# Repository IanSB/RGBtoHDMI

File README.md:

# RGBtoHDMI

The RGBtoHDMI interface converts the "digital" RGB video signal from
the BBC Micro or Electron to HDMI compatible with most modern
TV/Monitors. The interface comprises a Raspberry Pi Zero and a
specially designed Hat containing a small CPLD. Custom firmware on the
Raspberry Pi, in conjunction with the CPLD, is able to correctly
sample each of the Beeb's video modes to give a pixel-perfect
rendition.

For more information, see the project [Wiki](../../wiki).  
Assembled boards available here:  
https://github.com/IanSB/RGBtoHDMI/wiki/Assembled-boards-for-sale

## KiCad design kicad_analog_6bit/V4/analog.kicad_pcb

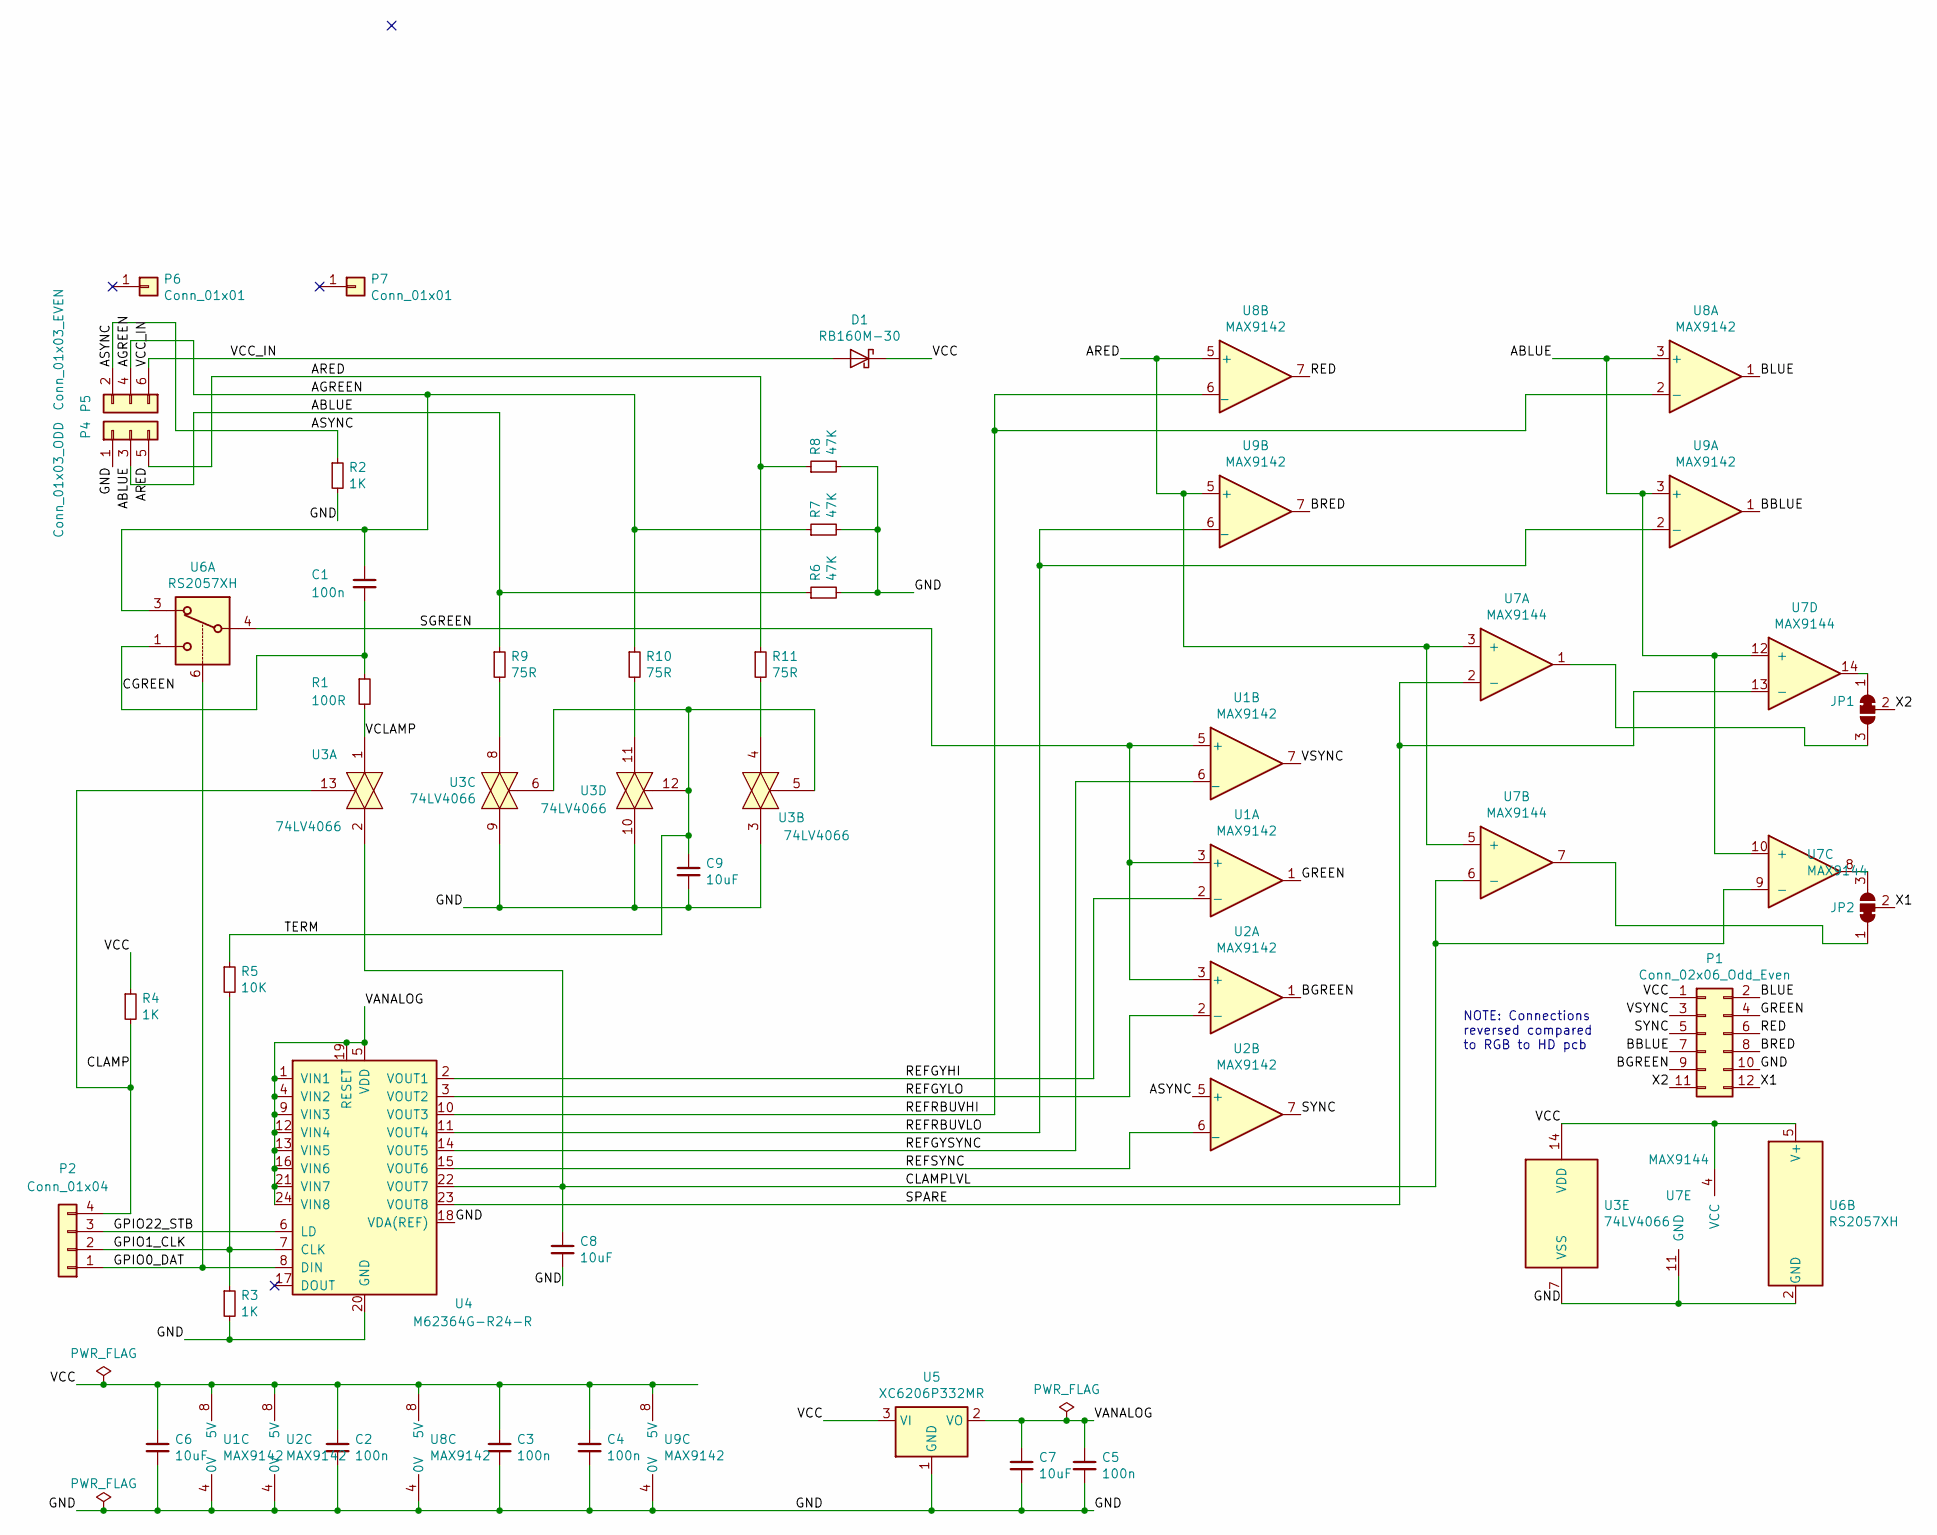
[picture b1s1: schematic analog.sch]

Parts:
C1, C2, C3, C4, C5: 100n; C_0805_2012Metric_Pad1.15x1.40mm_HandSolder
C6, C7, C8, C9: 10uF; C_0805_2012Metric_Pad1.15x1.40mm_HandSolder
D1: RB160M-30; D_SOD-123
JP1, JP2: SolderJumper_3_Bridged12; SolderJumper-3_P1.3mm_Bridged12_RoundedPad1.0x1.5mm
P1: Conn_02x06_Odd_Even; PinSocket_2x06_P2.54mm_Horizontal
P2: Conn_01x04; PinHeader_1x04_P2.54mm_Vertical
P4: Conn_01x03_ODD; Harwin_M20-89003xx_1x03_P2.54mm_Horizontal_Custom_ODD2
P5: Conn_01x03_EVEN; Harwin_M20-89003xx_1x03_P2.54mm_Horizontal_Custom_EVEN2
P6, P7: Conn_01x01; PinHeader_1x01_P2.54mm_Vertical
R1: 100R; R_0805_2012Metric_Pad1.15x1.40mm_HandSolder
R2, R3, R4: 1K; R_0805_2012Metric_Pad1.15x1.40mm_HandSolder
R5: 10K; R_0805_2012Metric_Pad1.15x1.40mm_HandSolder
R6, R7, R8: 47K; R_0805_2012Metric_Pad1.15x1.40mm_HandSolder
R9, R10, R11: 75R; R_0805_2012Metric_Pad1.15x1.40mm_HandSolder
U1, U2, U8, U9: MAX9142; SOIC-8_3.9x4.9mm_P1.27mm
U3: 74LV4066; TSSOP-14_4.4x5mm_P0.65mm
U4: M62364G-R24-R; SSOP-24_5.3x8.2mm_P0.65mm
U5: XC6206P332MR; SOT-23_Handsoldering
U6: RS2057XH; SOT-23-6_Handsoldering
U7: MAX9144; SOIC-14_3.9x8.7mm_P1.27mm

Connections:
/ABLUE: P4.3, R6.1, R9.1, U7.10 (+), U7.12 (+), U8.3 (+), U9.3 (+)
/AGREEN: C1.1, P5.4, R7.1, R10.1, U6.3
/ARED: P4.5, R8.1, R11.1, U7.3 (+), U7.5 (+), U8.5 (+), U9.5 (+)
/ASYNC: P5.2, R2.1, U2.5 (+)
/BBLUE: P1.7, U9.1
/BGREEN: P1.9, U2.1
/BLUE: P1.2, U8.1
/BRED: P1.8, U9.7
/CGREEN: C1.2, R1.1, U6.1
/CLAMP: P2.4, R4.2, U3.13
/CLAMPLVL: C8.1, U3.2, U4.22 (VOUT7), U7.6 (-), U7.9 (-)
/GND: C2.2, C3.2, C4.2, C5.2, C6.2, C7.2, C8.2, C9.2, P1.10, P4.1, R2.2, R3.2, R6.2, R7.2, R8.2, U1.4 (0V), U2.4 (0V), U3.3, U3.7 (VSS), U3.9, U3.10, U4.18 (VDA(REF)), U4.20 (GND), U5.1 (GND), U6.2 (GND), U7.11 (GND), U8.4 (0V), U9.4 (0V)
/GPIO0_DAT: P2.1, U4.8 (DIN), U6.6
/GPIO1_CLK: P2.2, R3.1, R5.2, U4.7 (CLK)
/GPIO22_STB: P2.3, U4.6 (LD)
/GREEN: P1.4, U1.1
/RED: P1.6, U8.7
/REFGYHI: U1.2 (-), U4.2 (VOUT1)
/REFGYLO: U2.2 (-), U4.3 (VOUT2)
/REFGYSYNC: U1.6 (_), U4.14 (VOUT5)
/REFRBUVHI: U4.10 (VOUT3), U8.2 (-), U8.6 (_)
/REFRBUVLO: U4.11 (VOUT4), U9.2 (-), U9.6 (_)
/REFSYNC: U2.6 (_), U4.15 (VOUT6)
/SGREEN: U1.3 (+), U1.5 (+), U2.3 (+), U6.4
/SPARE: U4.23 (VOUT8), U7.2 (-), U7.13 (-)
/SYNC: P1.5, U2.7
/TERM: C9.1, R5.1, U3.5, U3.6, U3.12
/VANALOG: C5.1, C7.1, U4.1 (VIN1), U4.4 (VIN2), U4.5 (VDD), U4.9 (VIN3), U4.12 (VIN4), U4.13 (VIN5), U4.16 (VIN6), U4.19 (RESET), U4.21 (VIN7), U4.24 (VIN8), U5.2 (VO)
/VCC: C2.1, C3.1, C4.1, C6.1, D1.1 (K), P1.1, R4.1, U1.8 (5V), U2.8 (5V), U3.14 (VDD), U5.3 (VI), U6.5 (V+), U7.4 (VCC), U8.8 (5V), U9.8 (5V)
/VCC_IN: D1.2 (A), P5.6
/VCLAMP: R1.2, U3.1
/VSYNC: P1.3, U1.7
/X1: JP2.2 (C), P1.12
/X2: JP1.2 (C), P1.11
unnamed: JP1.1 (A), U7.14
unnamed: JP1.3 (B), U7.1
unnamed: JP2.1 (A), U7.7
unnamed: JP2.3 (B), U7.8
unnamed: R9.2, U3.8
unnamed: R10.2, U3.11
unnamed: R11.2, U3.4

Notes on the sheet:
NOTE: Connections reversed compared to RGB to HD pcb

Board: 2 copper layers, 38 parts (6 on the bottom side), 41 nets, no tracks yet.

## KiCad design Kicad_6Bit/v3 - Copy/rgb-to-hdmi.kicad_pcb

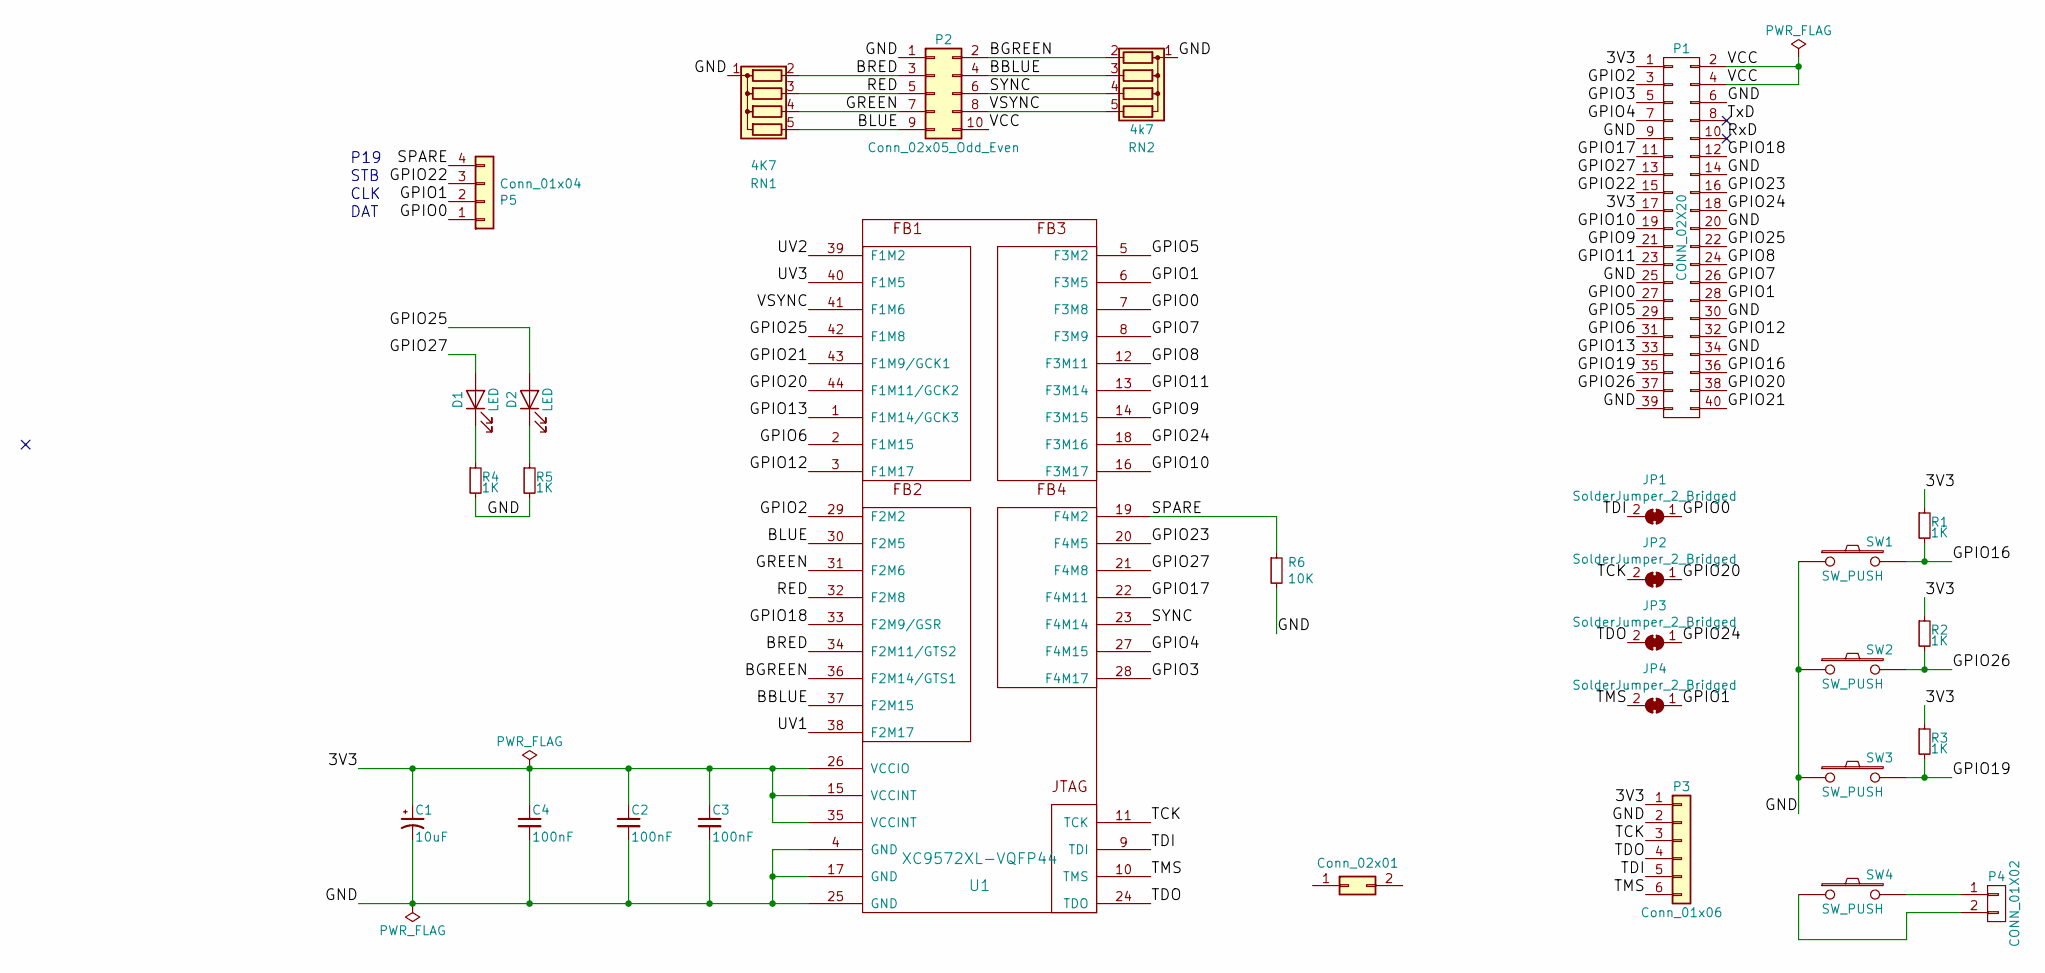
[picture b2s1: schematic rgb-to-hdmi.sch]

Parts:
C1: 10uF; C_0805_2012Metric_Pad1.15x1.40mm_HandSolder
C2, C3, C4: 100nF; C_0805_2012Metric_Pad1.15x1.40mm_HandSolder
D1, D2: LED; LED_D1.8mm_W3.3mm_H2.4mm
J2: Conn_02x01; PinHeader_2x01_P2.54mm_Horizontal
JP1, JP2, JP3, JP4: SolderJumper_2_Bridged; SolderJumper-2_P1.3mm_Bridged_RoundedPad1.0x1.5mm
P1: CONN_02X20; PinSocket_2x20_P2.54mm_Vertical
P2: Conn_02x05_Odd_Even; PinHeader_2x05_P2.54mm_Horizontal
P3: Conn_01x06; PinHeader_1x06_P2.54mm_Vertical
P4: CONN_01X02; PinSocket_1x02_P2.54mm_Vertical
P5: Conn_01x04; PinSocket_1x04_P2.54mm_Vertical
R1, R2, R3, R4, R5: 1K; R_0805_2012Metric_Pad1.15x1.40mm_HandSolder
R6: 10K; R_0805_2012Metric_Pad1.15x1.40mm_HandSolder
RN1: 4K7; R_Array_SIP5
RN2: 4k7; R_Array_SIP5
SW1, SW2, SW3, SW4: SW_PUSH; SW_PUSH_6mm_H5mm
U1: XC9572XL-VQFP44; LQFP-44_10x10mm_P0.8mm

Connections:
/3V3: C1.1, C2.1, C3.1, C4.1, P1.1, P1.17, P3.1, R1.1, R2.1, R3.1, U1.15 (VCCINT), U1.26 (VCCIO), U1.35 (VCCINT)
/BBLUE: P2.4, RN2.3 (R2), U1.37 (F2M15)
/BGREEN: P2.2, RN2.2 (R1), U1.36 (F2M14/GTS1)
/BLUE: P2.9, RN1.5 (R4), U1.30 (F2M5)
/BRED: P2.3, RN1.2 (R1), U1.34 (F2M11/GTS2)
/GND: C1.2, C2.2, C3.2, C4.2, P1.6, P1.9, P1.14, P1.20, P1.25, P1.30, P1.34, P1.39, P2.1, P3.2, R4.2, R5.2, R6.2, RN1.1 (common), RN2.1 (common), SW1.1, SW2.1, SW3.1, U1.4 (GND), U1.17 (GND), U1.25 (GND)
/GPIO0: JP1.1 (A), P1.27, P5.1, U1.7 (F3M8)
/GPIO1: JP4.1 (A), P1.28, P5.2, U1.6 (F3M5)
/GPIO2: P1.3, U1.29 (F2M2)
/GPIO3: P1.5, U1.28 (F4M17)
/GPIO4: P1.7, U1.27 (F4M15)
/GPIO5: P1.29, U1.5 (F3M2)
/GPIO6: P1.31, U1.2 (F1M15)
/GPIO7: P1.26, U1.8 (F3M9)
/GPIO8: P1.24, U1.12 (F3M11)
/GPIO9: P1.21, U1.14 (F3M15)
/GPIO10: P1.19, U1.16 (F3M17)
/GPIO11: P1.23, U1.13 (F3M14)
/GPIO12: P1.32, U1.3 (F1M17)
/GPIO13: P1.33, U1.1 (F1M14/GCK3)
/GPIO16: P1.36, R1.2, SW1.2
/GPIO17: P1.11, U1.22 (F4M11)
/GPIO18: P1.12, U1.33 (F2M9/GSR)
/GPIO19: P1.35, R3.2, SW3.2
/GPIO20: JP2.1 (A), P1.38, U1.44 (F1M11/GCK2)
/GPIO21: P1.40, U1.43 (F1M9/GCK1)
/GPIO22: P1.15, P5.3; also elsewhere on the board
/GPIO23: P1.16, U1.20 (F4M5)
/GPIO24: JP3.1 (A), P1.18, U1.18 (F3M16)
/GPIO25: D2.2 (A), P1.22, U1.42 (F1M8)
/GPIO26: P1.37, R2.2, SW2.2
/GPIO27: D1.2 (A), P1.13, U1.21 (F4M8)
/GREEN: P2.7, RN1.4 (R3), U1.31 (F2M6)
/RED: P2.5, RN1.3 (R2), U1.32 (F2M8)
/RxD: P1.10
/SPARE: P5.4, R6.1, U1.19 (F4M2); also elsewhere on the board
/SYNC: P2.6, RN2.4 (R3), U1.23 (F4M14)
/TCK: JP2.2 (B), P3.3, U1.11 (TCK)
/TDI: JP1.2 (B), P3.5, U1.9 (TDI)
/TDO: JP3.2 (B), P3.4, U1.24 (TDO)
/TMS: JP4.2 (B), P3.6, U1.10 (TMS)
/TxD: P1.8
/UV1: U1.38 (F2M17)
/UV2: U1.39 (F1M2)
/UV3: U1.40 (F1M5)
/VCC: P1.2, P1.4, P2.10
/VSYNC: P2.8, RN2.5 (R4), U1.41 (F1M6)
unnamed: D1.1 (K), R4.1
unnamed: D2.1 (K), R5.1
unnamed: P4.1, SW4.2
unnamed: P4.2, SW4.1

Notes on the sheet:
DAT
CLK
STB
P19

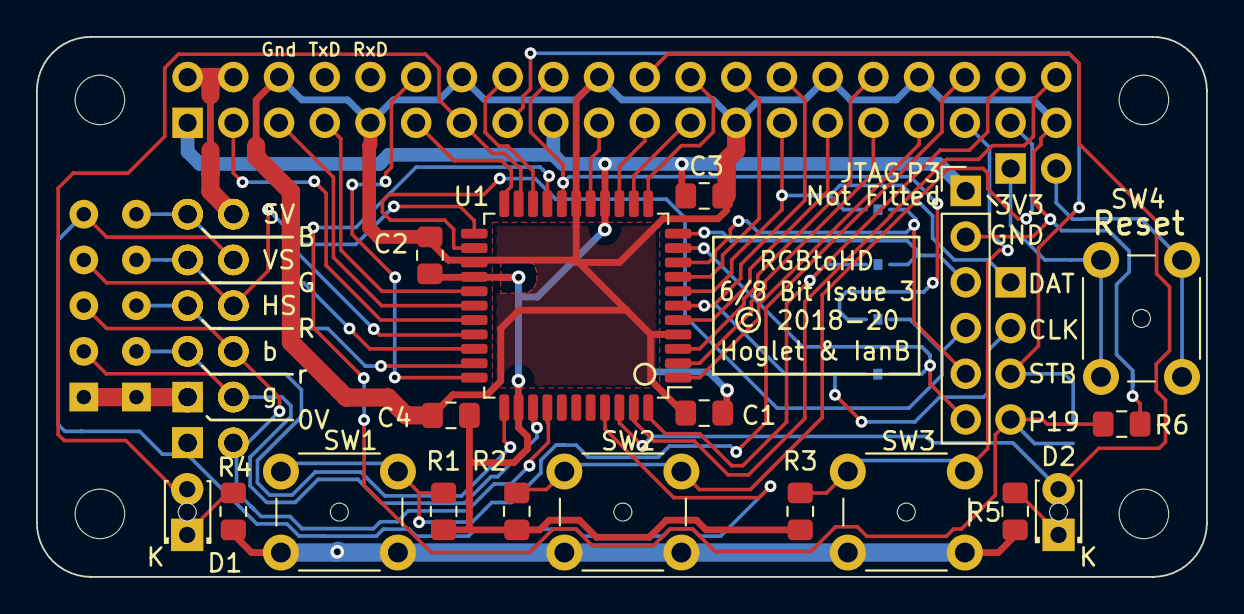
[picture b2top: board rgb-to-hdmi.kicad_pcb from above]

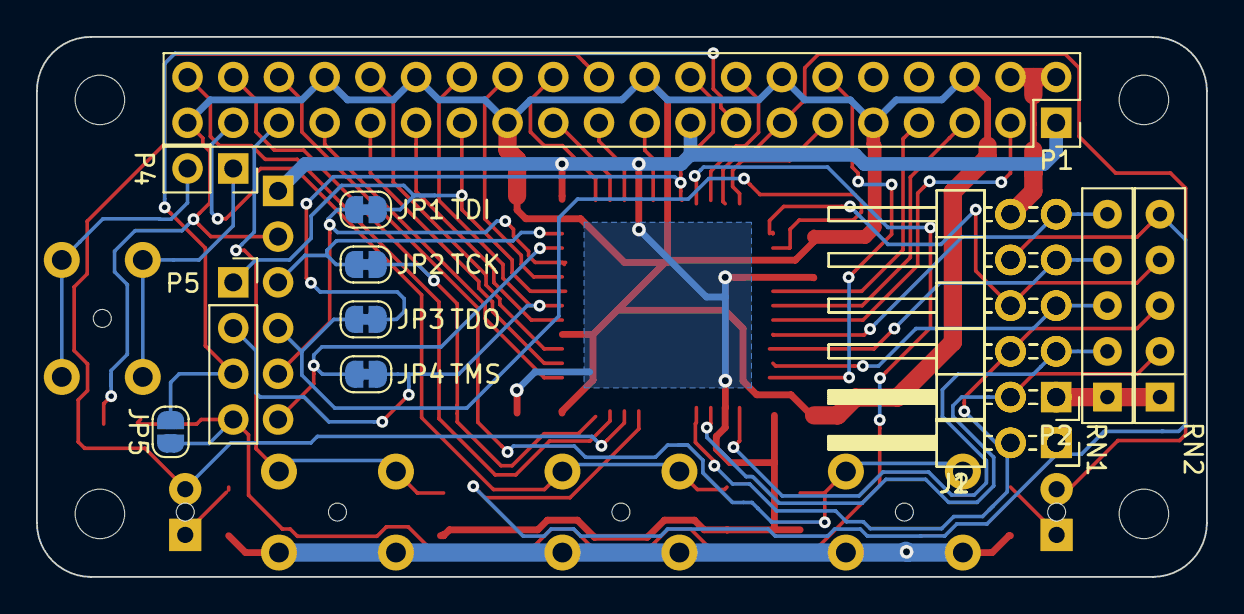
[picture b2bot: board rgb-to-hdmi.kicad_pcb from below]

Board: 2 copper layers, 65.0 x 30.0 mm, 37 parts (13 on the bottom side), 46 nets.

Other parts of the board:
 : mountinghole_1mm
 #2,  #3,  #4,  #5,  #6: mountinghole_1mm
J1: Conn_02x06_Odd_Even; PinHeader_2x06_P2.54mm_Horizontal
JP5: SolderJumper_2_Open; SolderJumper-2_P1.3mm_Open_RoundedPad1.0x1.5mm

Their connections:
/GPIO22: JP5.2; also elsewhere on the board
/SPARE: JP5.1; also elsewhere on the board

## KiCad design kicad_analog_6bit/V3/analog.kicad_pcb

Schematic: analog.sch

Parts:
C1, C2, C3, C4, C5: 100n; C_0805_2012Metric_Pad1.15x1.40mm_HandSolder
C6, C7, C8, C9: 10uF; C_0805_2012Metric_Pad1.15x1.40mm_HandSolder
D1: D_Schottky; D_0805_2012Metric_Pad1.15x1.40mm_HandSolder
JP1, JP2: SolderJumper_3_Bridged12; SolderJumper-3_P1.3mm_Bridged12_RoundedPad1.0x1.5mm
P1: Conn_02x06_Odd_Even; PinSocket_2x06_P2.54mm_Horizontal
P2: Conn_01x04; PinHeader_1x04_P2.54mm_Vertical
P3: Conn_01x06; Molex_PicoBlade_53048-0610_1x06_P1.25mm_Horizontal
P6, P7: Conn_01x01; PinHeader_1x01_P2.54mm_Vertical
R1: 75R; R_0805_2012Metric_Pad1.15x1.40mm_HandSolder
R2, R3, R4: 1K; R_0805_2012Metric_Pad1.15x1.40mm_HandSolder
R5, R6, R7, R8: 10K; R_0805_2012Metric_Pad1.15x1.40mm_HandSolder
R9, R10, R11: 68R; R_0805_2012Metric_Pad1.15x1.40mm_HandSolder
U1, U2: MAX9108; SOIC-14_3.9x8.7mm_P1.27mm
U3: MAX4610; SOIC-14_3.9x8.7mm_P1.27mm
U4: MAX5259EEE+; QSOP-16_3.9x4.9mm_P0.635mm
U5: MCP1754S-3302xCB; SOT-23_Handsoldering
U6: TS5A3159ADBVR; SOT-23-6_Handsoldering
U7: MAX9108-Comparator; SOIC-14_3.9x8.7mm_P1.27mm

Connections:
/ABLUE: P3.3, R6.1, R9.1, U2.3 (+), U2.5 (+), U7.10 (+), U7.12 (+)
/AGREEN: C1.1, P3.4, R7.1, R10.1, U6.3
/ARED: P3.5, R8.1, R11.1, U2.10 (+), U2.12 (+), U7.3 (+), U7.5 (+)
/ASYNC: P3.2, R2.1, U1.10 (+)
/BBLUE: P1.7, U2.7
/BGREEN: P1.9, U1.7
/BLUE: P1.2, U2.1
/BRED: P1.8, U2.8
/CGREEN: C1.2, R1.1, U6.1
/CLAMP: P2.4, R4.2, U3.13
/CLAMPLVL: C8.1, U3.2, U4.9 (OUTG), U7.6 (-), U7.9 (-)
/GND: C2.2, C3.2, C4.2, C5.2, C6.2, C7.2, C8.2, C9.2, P1.10, P3.1, R2.2, R3.2, R6.2, R7.2, R8.2, U1.11 (GND), U2.11 (GND), U3.3, U3.7 (VSS), U3.9, U3.10, U4.3 (GND), U4.6 (LDAC), U5.1 (GND), U6.2, U7.11 (GND)
/GPIO0_DAT: P2.1, U4.13 (DIN), U6.6
/GPIO1_CLK: P2.2, R3.1, R5.2, U4.12 (SCLK)
/GPIO22_STB: P2.3, U4.11 (CS)
/GREEN: P1.4, U1.1
/RED: P1.6, U2.14
/REFGYHI: U1.2 (-), U4.2 (OUTA)
/REFGYLO: U1.6 (-), U4.1 (OUTB)
/REFGYSYNC: U1.13 (-), U4.7 (OUTE)
/REFRBUVHI: U2.2 (-), U2.13 (-), U4.16 (OUTC)
/REFRBUVLO: U2.6 (-), U2.9 (-), U4.15 (OUTD)
/REFSYNC: U1.9 (-), U4.8 (OUTF)
/SGREEN: U1.3 (+), U1.5 (+), U1.12 (+), U6.4
/SPARE: U4.10 (OUTH), U7.2 (-), U7.13 (-)
/SYNC: P1.5, U1.8
/TERM: C9.1, R5.1, U3.5, U3.6, U3.12
/UV1: JP1.2, P1.11
/UV2: JP2.2, P1.12
/VANALOG: C5.1, C7.1, U4.4 (VDD), U4.5 (REF), U5.2 (VO)
/VCC: C2.1, C3.1, C4.1, C6.1, D1.1 (K), P1.1, R4.1, U1.4 (VCC), U2.4 (VCC), U3.14 (VDD), U5.3 (VI), U6.5, U7.4 (VCC)
/VCC_IN: D1.2 (A), P3.6
/VCLAMP: R1.2, U3.1
/VSYNC: P1.3, U1.14
unnamed: JP1.1, U7.14
unnamed: JP1.3, U7.1
unnamed: JP2.1, U7.7
unnamed: JP2.3, U7.8
unnamed: R9.2, U3.8
unnamed: R10.2, U3.11
unnamed: R11.2, U3.4

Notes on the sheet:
NOTE: Connections reversed compared to RGB to HD pcb

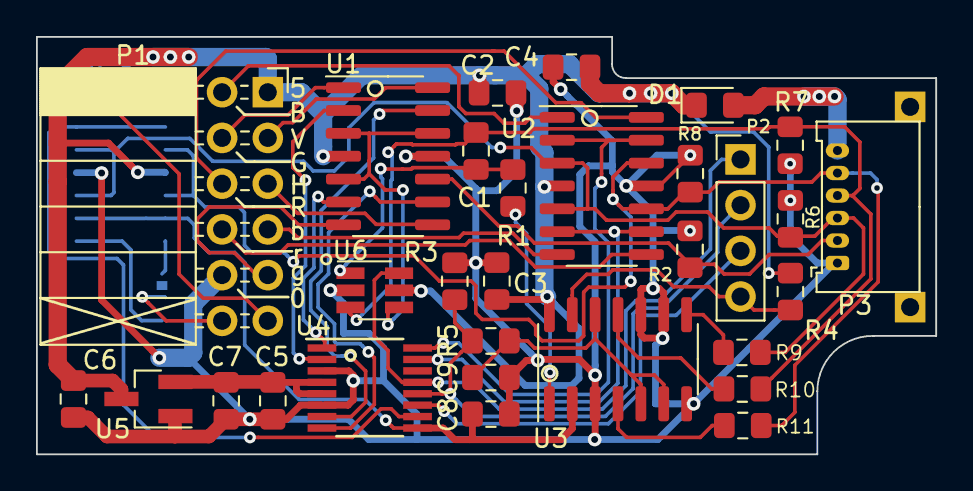
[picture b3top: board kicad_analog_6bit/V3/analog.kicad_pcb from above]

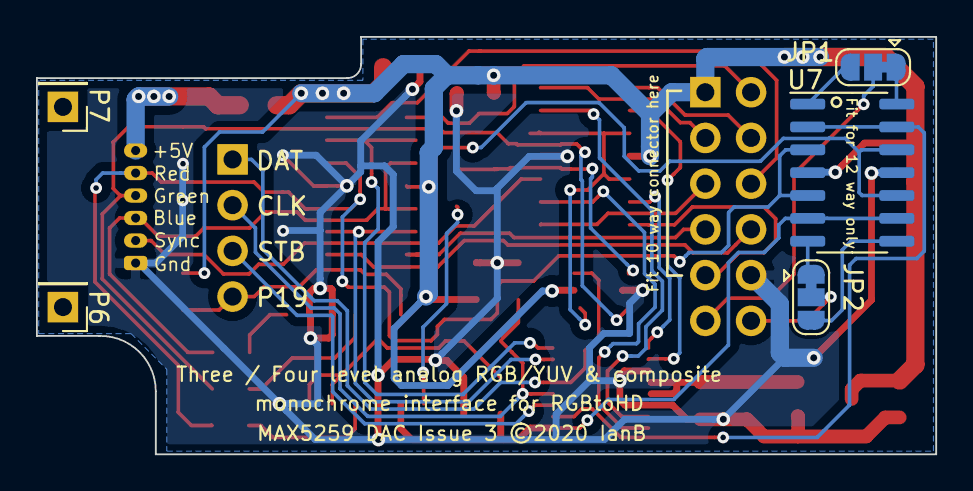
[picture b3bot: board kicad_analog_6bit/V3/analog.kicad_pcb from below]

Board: 2 copper layers, 50.0 x 23.2 mm, 35 parts (5 on the bottom side), 41 nets.

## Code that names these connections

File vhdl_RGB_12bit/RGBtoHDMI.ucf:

# Global Clock Nets
NET "clk" BUFG=CLK;

# 96MHz clock domain
NET "clk" TNM_NET = clk_period_grp_1;
TIMESPEC TS_clk_period_1 = PERIOD "clk_period_grp_1" 5.2ns HIGH;


NET "clk"       LOC = "P43";       # input  gpio21 (gclk)

NET "R3_I"      LOC = "P32";       # input
NET "G3_I"      LOC = "P31";       # input
NET "B3_I"      LOC = "P30";       # input
NET "R2_I"      LOC = "P34";       # input
NET "G2_I"      LOC = "P36";       # input
NET "B2_I"      LOC = "P37";       # input
NET "R1_I"      LOC = "P39";       # input  (was gpio26)
NET "G1_I"      LOC = "P40";       # input  (was gpio19)
NET "B1_I"      LOC = "P38";       # input  (was gpio16)
NET "R0_I"      LOC = "P21";       # input  (was gpio27)
NET "G0_I"      LOC = "P42";       # input  (was gpio25)
NET "B0_I"      LOC = "P18";       # input  (was gpio24)

NET "csync_I"   LOC = "P23";       # input
NET "vsync_I"   LOC = "P41";       # input  (connects to vsync)

NET "analog"    LOC = "P19";       # input  gpio22

NET "version"   LOC = "P33";       # input  gpio18 (gsr)

NET "sp_clken"  LOC = "P6";        # input  gpio1  (input only)

NET "quad(0)"   LOC = "P29";       # output gpio2
NET "quad(1)"   LOC = "P28";       # output gpio3
NET "quad(2)"   LOC = "P27";       # output gpio4
NET "quad(3)"   LOC = "P5";        # output gpio5
NET "quad(4)"   LOC = "P2";        # output gpio6
NET "quad(5)"   LOC = "P8";        # output gpio7
NET "quad(6)"   LOC = "P12";       # output gpio8
NET "quad(7)"   LOC = "P14";       # output gpio9
NET "quad(8)"   LOC = "P16";       # output gpio10
NET "quad(9)"   LOC = "P13";       # output gpio11
NET "quad(10)"  LOC = "P3";        # output gpio12
NET "quad(11)"  LOC = "P1";        # output gpio13

NET "psync"     LOC = "P22";       # output gpio17
NET "csync"     LOC = "P20";       # output gpio23

NET "quad(0)"   SLOW;
NET "quad(1)"   SLOW;
NET "quad(2)"   SLOW;
NET "quad(3)"   SLOW;
NET "quad(4)"   SLOW;
NET "quad(5)"   SLOW;
NET "quad(6)"   SLOW;
NET "quad(7)"   SLOW;
NET "quad(8)"   SLOW;
NET "quad(9)"   SLOW;
NET "quad(10)"  SLOW;
NET "quad(11)"  SLOW;
NET "psync"     SLOW;
NET "csync"     SLOW;

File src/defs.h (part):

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#define MAX_PIXEL_CLOCK     340.0 // 340MHz
#endif

// Enable multiple buffering and vsync based page flipping
#define MULTI_BUFFER

// The maximum number of buffers used by multi-buffering
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#define BIT_INTERLACED_VIDEO            0x80   // bit  7, if set then interlaced video detected or teletext enabled
#define BIT_CLEAR                      0x100   // bit  8, indicates the frame buffer should be cleared
#define BITDUP_ENABLE_FFOSD             0x100   // bit  8, indicates FFOSD is enabled
#define BIT_VSYNC                      0x200   // bit  9, indicates the red v sync indicator should be displayed
#define BIT_VSYNC_MARKER               0x400   // bit 10, indicates current line should be replaced by the red vsync indicator
#define BIT_DEBUG                      0x800   // bit 11, indicates the debug grid should be displayed

#define OFFSET_LAST_BUFFER 12        // bit 12-13 LAST_BUFFER
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#define GPLEV0_OFFSET     0x000034

#if defined(RPI4)
#define INTPEND2_OFFSET   0x00B204    //SMI interrupt (GPU # 48 used for vsync) is actually in IRQ0_PENDING1 on pi 4 (0xfe00b204)
#define PV2_INTSTAT       0x20a028
#else
#define INTPEND2_OFFSET   0x00B208
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#define GPIO_PULLDOWN   0x01
#define GPIO_PULLUP     0x02

#define SYNC_BIT_HSYNC_INVERTED   0x01      // bit  0, indicates hsync/composite sync is inverted
#define SYNC_BIT_VSYNC_INVERTED   0x02      // bit  1, indicates vsync is inverted
#define SYNC_BIT_COMPOSITE_SYNC   0x04      // bit  2, indicates composite sync
#define SYNC_BIT_MIXED_SYNC       0x08      // bit  3, indicates H and V syncs eored in CPLD
#define SYNC_BIT_INTERLACED       0x10      // bit  4, indicates interlaced sync detected
#define SYNC_BIT_MASK             0x07      // masks out bits 3 + 4

#define VSYNC_RETRY_MAX 10
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#define NTSC_Y_INVERT           0x20
#define NTSC_LAST_ARTIFACT      0x40
#define NTSC_LAST_ARTIFACT_SHIFT   6
#define NTSC_HDMI_BLANK_ENABLE  0x80        //not actually ntsc but uses a spare bit
#define NTSC_LAST_IIGS         0x100        //not actually ntsc but uses a spare bit
#define NTSC_LAST_IIGS_SHIFT       8
#define NTSC_FFOSD_ENABLE      0x200        //not actually ntsc but uses a spare bit
#define NTSC_DONE_FIRST        0x400
#define NTSC_RGB_INVERT        0x800

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#define YUV_VERSION 0x91

//these defines are adjusted for different clock speeds
#define FIELD_TYPE_THRESHOLD_BBC 39000            //  post frame sync times are ~22uS & ~54uS on beeb and ~34uS and ~66uS on Amiga so threshold of 45uS covers both
#define FIELD_TYPE_THRESHOLD_AMIGA 45000          //  post frame sync times are ~22uS & ~54uS on beeb and ~34uS and ~66uS on Amiga so threshold of 45uS covers both
#define ELK_LO_FIELD_SYNC_THRESHOLD 150000  // 150uS
#define ELK_HI_FIELD_SYNC_THRESHOLD 170000  // 170uS
#define ODD_THRESHOLD 22500
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#define BBC_HSYNC_THRESHOLD 6144
#define NORMAL_HSYNC_THRESHOLD 9000
#define BLANKING_HSYNC_THRESHOLD 14000
#define EQUALISING_THRESHOLD 3400      // equalising pulses are half sync pulse length and must be filtered out
#define FRAME_MINIMUM 10000000         // 10ms
#define FRAME_TIMEOUT 30000000         // 30ms which is over a frame / field @ 50Hz (20ms)
#define LINE_MINIMUM 10000             // 10uS
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
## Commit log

2020-02-16 Experimental V3 analog layout using GPIOs 0 & 1 to control termination
2020-02-16 Separate termination of Y & UV controlled from GPIO 0 & 1
2020-02-16 Support inverted termination including CPLD programming
2020-02-16 Update issue 3 with normally closed DG441
2020-02-17 Analog V3 non-inverted 14 pin
2020-02-17 Update profiles
2020-02-18 V3 PCB layout with MAX4610
2020-02-18 Change CPLD programming to have an average voltage below the logic 0 threshold
2020-02-18 Update code for latest analog hardware mods
2020-02-19 Update pcb with AC/DC switch
2020-02-19 Update for AC/DC input option
2020-02-21 V3 pcb plus some older alternatives
2020-02-21 Tweaks to V3 analog PCB
2020-02-22 Updated analog board
2020-02-22 Updated 8 bit
2020-02-22 Updated 8 bit hat
2020-02-22 Update profiles for ac/dc coupling
2020-02-22 Update ac/dc switch and analog driver
2020-06-17 Initial Circuit for issue 4
2021-07-05 Add support for CPLD v94 with 9 bpp + blank and 1bpp on vsync
2021-07-05 Further support for 1bpp vsync and auto config sample phasing
2021-07-06 Ignore flashing cursors when auto calibrating
2021-07-06 Optimise line capture loop and fix edge bug in NTSC artifact mode
2021-07-06 Improve sync loss handling
2021-07-06 Fix equivalence calculation
2021-10-29 Mark screen as cacheable
2021-10-29 Add L1 data cache clean
2022-01-01 Correct return value
    Return value of 0 = error
2024-01-25 Use parallel register transfer
2024-03-12 Add Nascom 1 & update Nascom 2 profiles
2024-03-12 Update test profiles
2024-03-12 Add Zenith Z110 profile
2024-03-17 Update default profile
2024-03-17 Update C64 profiles
2024-03-17 Update Sam Coupe profile
2024-03-17 Update 2560x1440 resolution
2024-03-17 Add 2560x1600 and 2048x1536 resolutions
2024-03-17 Add integer scaling preference setting and fix some scaling issues
2024-03-19 Fix some more integer scaling issues and add 9 bit lumacode
2024-03-20 Add support for 2560x1600 resolution
2024-03-20 Force DVI mode when auto detecting for blacklisted monitors
2024-03-24 Invert logic of _ profile hiding with mono/lumacode boards
2024-03-24 Update profiles for inverted _ hiding logic
2024-03-24 Add TI-990 VDT911 50Hz profile
2024-03-25 Further updates for inverted _ logic
2024-04-06 Update monitor blacklist
2024-04-23 Add BBC CPLD Limited Test profile
2024-04-23 Update BBC Nula profiles
2024-04-23 Update firmware
2024-04-23 Update default.txt in Amiga configs
2024-04-23 Update default.txt handling for single button mode and cpld firmware dir
2024-05-01 Update Mac profiles
2024-05-08 Reverse order of mode7 calibration
2024-05-08 Initial HDMI audio support including WAV player
2024-05-12 Clear screen when loading wav
2024-05-12 Update wav logging
2024-05-13 Move GPU capture code from VPU1 to VPU0
2024-06-14 Update NuLA profiles
2024-06-15 Update profiles for v9.5 RGB firmware
2024-06-16 Add mono palette option for analog V/Hsync, fix firmware update message & fix hang with GPU capture
2024-06-16 Update CPLD firmware release folder
2024-06-16 Add border setting to create profile menu
2024-06-16 Remove dedicated sync register in GPU comms
2024-06-17 Add analog profiles for video(B)+Hsync(S)+Vsync(G) sources
2024-06-30 Add zx81 vLA81 profile
2024-06-30 Change GPU comms to use 7 data registers
2024-09-08 Revert order of mode 7 calibration
2024-10-15 Update BBC digital test profiles
2024-10-15 Update BBC analog test profiles
2024-10-15 Update RGB test profiles
2024-10-15 Update RGB analog test profiles
2024-10-15 Update YUV test profiles
2024-10-15 Update YUV analog test profiles
2024-10-15 Update legacy test profiles
2024-10-15 Move UK101 profile
2024-10-15 Add Compustar II profile
2024-10-15 Fix TRS80 60Hz profile
2024-10-15 Fix Apple I profile
2024-10-15 Emphasize jumper resoldering message
2024-10-15 Extend clock tolerance limit
2024-11-08 Update base profiles
2024-11-08 Improve CPLD Update check
2024-12-10 Add 720x576 @100/120Hz
2024-12-10 Add support for 2160x1440 resolution
2024-12-10 Update Acorn System 5 80 column profile
2024-12-10 Update test profiles with composite sync support
2024-12-10 Update Apple IIGS profile
2024-12-19 Add support for 1920x1280 resolution
2024-12-29 Add corvus concept profile
2024-12-29 Update analog base profiles
2024-12-30 Update NES support
2024-12-30 Add simple mode test profiles
2024-12-30 Update test profile
2024-12-30 Update NES profiles
2024-12-30 Fix mode change reboot message not displayed in 4 & 8bpp modes
2025-01-23 Update VIC20 palette, add Video 7 palette & add customised default resolution feature for specific monitors or adapters
2025-01-23 Add Apple IIe video7 profile
2025-01-23 Add VT100 & VT220 profiles
2025-01-23 Add C128 mono profiles
2025-01-29 Add Atari 2600 no genlock profile
2025-03-17 Add some resolutions inc 1920x1080 interlaced
2025-03-17 Add BFZ-MFA profile
2025-03-22 Add audio capture support
2025-03-22 Update profiles with audio setting
2025-03-22 Enforce firmware 9.5
2025-03-23 Update profiles with audio capture enabled
2025-03-23 Add auto overclocking to audio optimise option
2025-03-23 Increase idle loop
2025-03-23 Limit DMA delay to 3ms min
2025-03-23 Update videocore
2025-03-24 Update audio optimise & enums
2025-03-24 Fix auto detection of GPIO connections
2025-03-25 Fix power on message
2025-03-26 Fix amber colour
2025-03-28 Update profiles for mono/stereo
2025-03-28 Add audio mode option
2025-03-29 Handle full/empty error conditions, improve core overclock
2025-03-30 Update logging and audio defines
2025-03-31 Change connection nomenclature from 'N' and 'R' to 'L' (LED) and 'F' (FFOSD)
2025-04-01 Further nomenclature changes
2025-04-02 Fix can't disable FFOSD in simple mode
2025-04-05 Invert audio
2025-04-22 Add experimental interrupt support
2025-04-25 Update some profiles
2025-04-25 Add G7000 Master system and Intellivision lumacode palettes
2025-04-25 Stop audio during CPLD programming
2025-04-28 Change default audio configuration and update profiles
2025-04-28 Fix Sega Master System palette
2025-05-24 Update profiles including Nascom 2 & Amstrad CPC + add TTL profiles for older mono computers

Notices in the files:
Kicad_6Bit/v3 - Copy/rgb-to-hdmi.kicad_pcb:
© 2018-20
kicad_analog_6bit/V3/analog.kicad_pcb:
MAX5259 DAC Issue 3 ©2020 IanB
kicad_analog_6bit/V4/analog.kicad_pcb:
BU2506FV DAC Issue 4 ©2020 IanB
